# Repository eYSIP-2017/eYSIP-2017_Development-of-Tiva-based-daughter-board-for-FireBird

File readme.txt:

This folder contains the work done on Tiva based daughter board.
It includes manuals, experiment codes, schematics, report etc.

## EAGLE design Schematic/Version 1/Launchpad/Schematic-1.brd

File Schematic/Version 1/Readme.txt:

The following are the bugs in the version 1 of Plug and Play board and uC based board.

Bugs:

Plug and Play Board:
1. 7805 Placement: The 7805 was not positioned at the end. Becuase of
this there was no sucient space to add the heat sink.
2. Port Expander Naming: The names of port expander are interchanged
in the Daughter board. The names of port expander printed on the
Daughter board are interchanged. Port B is named as port A and vice
versa.
3. Switch Connection : The switch is used to connect the Ground of
Launchpad and Daughter board for programming. The connections of
this switch is incorrect.
4. The bot has to powered rst and then micro USB should be connected
to program the bot. This is because of the absence of switch explained
in the previous step
5. LCD starts displaying data on alternate press of reset button. It gets
initialised everytime but fails to display data.
6. Buzzer and red LED of TIVA launchad are on the same pin. Certain
motors pins and red and green LED pins also overlap.

uC based Board:
1. RX and TX LEDs: LEDs attached to RX and TX pins of serial com-
munication are not woring. The bot is able to communicate with the
laptop serial but the LEDs are not glowing.
2. Crystal Placement: The Crystal is placed far from the microcontroller.
Because of this the inductance of wires may eect the crysal frequency.
3. Heat Sink: The heat sink provided for LM1117 is not sucient.
4. Naming : The names of port expamders, servo headers, programming
headers are not printer on the board. The names of SCL and SDA pins
on the board is interchanged i.e SCL pin is printed as SDA and vice
versa.
5. The bot does not get programmed everytime because of connection
problems.(Resolderig the pins of uC might help solve the problem)
6. LCD starts displaying data on alternate press of reset button. It gets
initialised everytime but fails to display data.

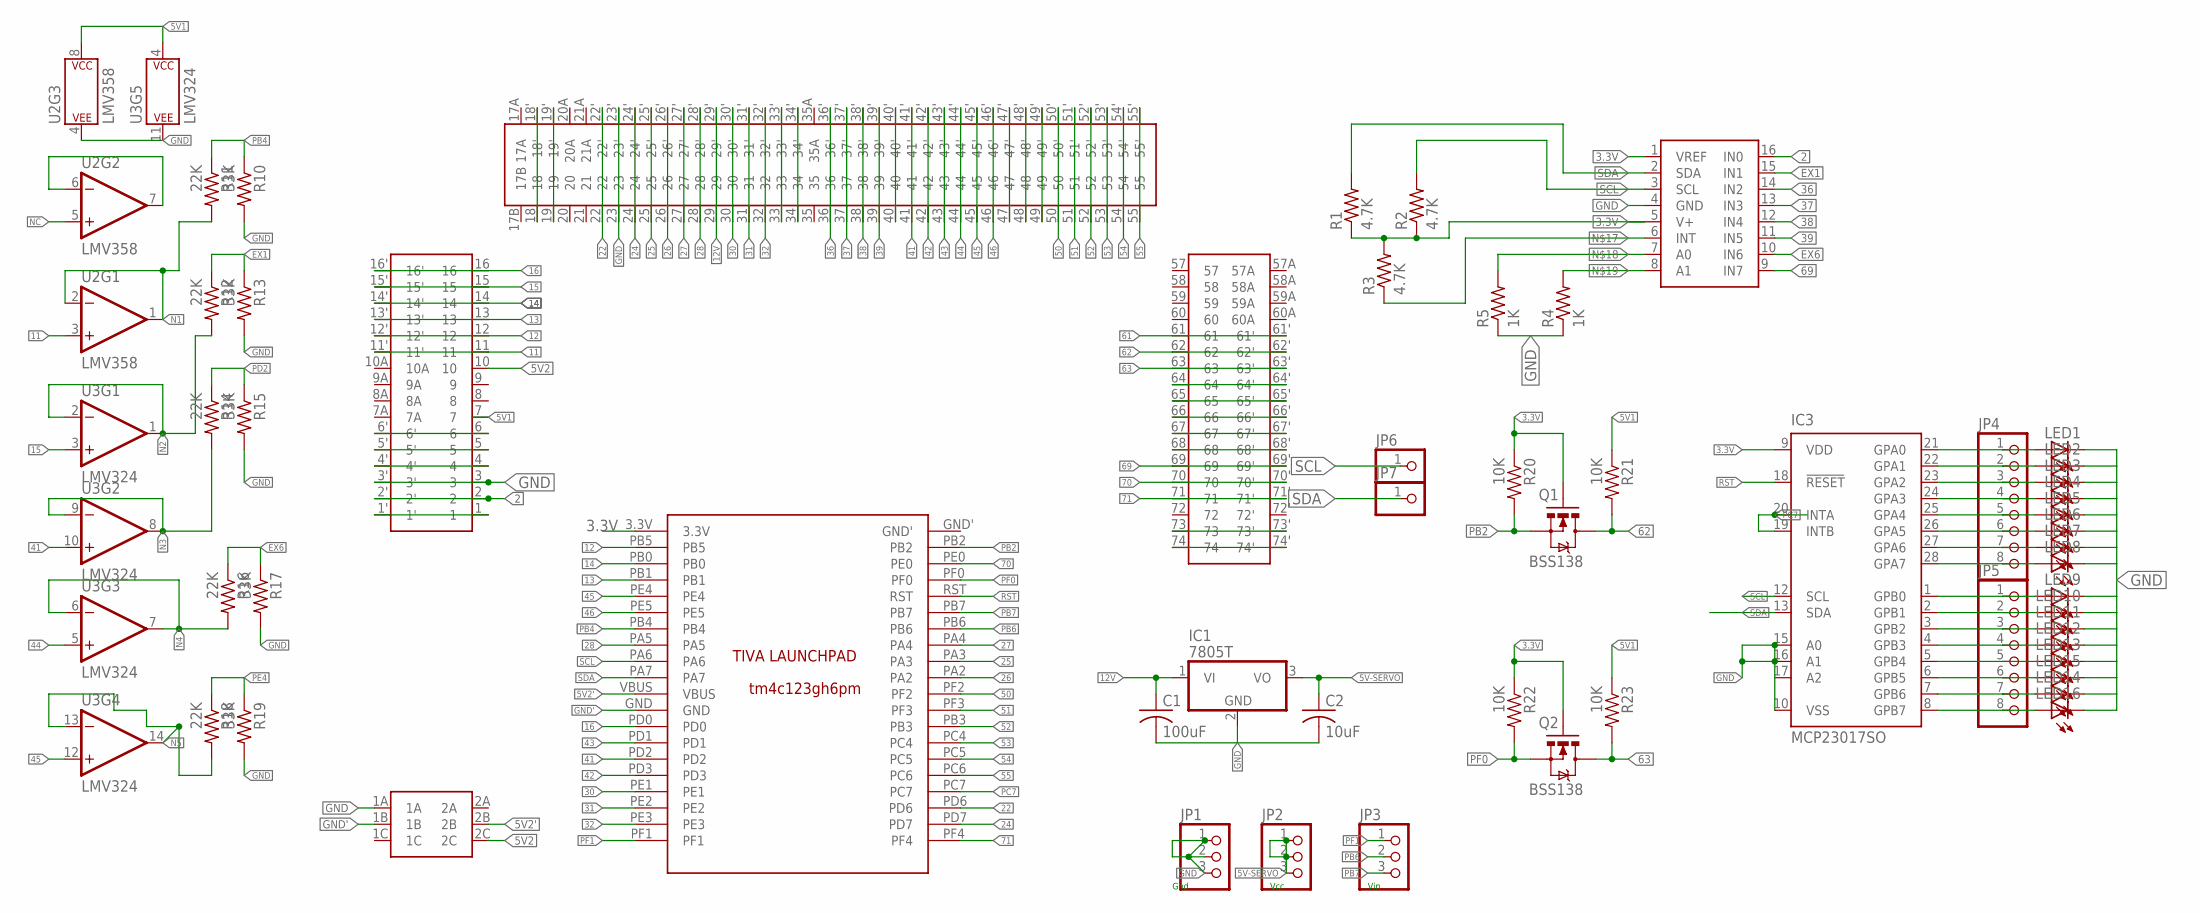
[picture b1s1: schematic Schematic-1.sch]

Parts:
C1: 100uF; C025-030X050
C2: 10uF; C025-030X050
IC1: 7805T; TO220H
IC3: MCP23017SO; SO28W
JP1, JP2, JP3: PINHD-1X3; 1X03
JP4, JP5: PINHD-1X8BIG; 1X08-BIG
JP6, JP7: PINHD-1X1; 1X01
LED1, LED2, LED3, LED4, LED5, LED6, LED7, LED8, LED9, LED10, LED11, LED12, LED13, LED14, LED15, LED16: LEDSMT1206; 1206
Q1, Q2: BSS138; SOT23-3
R1, R2, R3: 4.7K; M1206
R4, R5: 1K; M1206
R10, R13, R15, R17, R19: 33K; M1206
R11, R12, R14, R16, R18: 22K; M1206
R20, R21, R22, R23: 10K; 1206
U2: LMV358; SO08
U3: LMV324; SO14
U$1: DAUGHTERBOARDDAUGHTERBOARD; DAUGHTERBOARD
U$2: TIVA_LAUNCHPADTIVA_LAUNCHPAD; TIVA_LAUNCHPAD
U$3: SELF-LOCKING_SWITCHSELF-LOCKING_SWITCH; SELF-LOCKING_SWITCH
U$4: ADC128D818; ADC12_SD

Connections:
2: U$1.2, U$1.2', U$4.16 (IN0)
3.3V: IC3.9 (VDD), Q1.1 (G), Q2.1 (G), R1.1, R2.1, R3.2, R20.1, R22.1, U$2.3.3V, U$4.1 (VREF), U$4.5 (V+)
5V1: R21.1, R23.1, U2.8 (P$V+), U3.4 (P$V+), U$1.7
5V2: U$1.10, U$3.2C
5V2': U$2.VBUS, U$3.2B
5V-SERVO: C2.1, IC1.3 (VO), JP2.1, JP2.2, JP2.3
11: U2.3 (+IN), U$1.11, U$1.11'
12: U$1.12, U$1.12', U$2.PB5
12V: C1.1, IC1.1 (VI), U$1.29, U$1.29'
13: U$1.13, U$1.13', U$2.PB1
14: U$1.14, U$1.14', U$2.PB0
15: U3.3 (+IN), U$1.15, U$1.15'
16: U$1.16, U$1.16', U$2.PD0
22: U$1.22, U$1.22', U$2.PD6
24: U$1.24, U$1.24', U$2.PD7
25: U$1.25, U$1.25', U$2.PA3
26: U$1.26, U$1.26', U$2.PA2
27: U$1.27, U$1.27', U$2.PA4
28: U$1.28, U$1.28', U$2.PA5
30: U$1.30, U$1.30', U$2.PE1
31: U$1.31, U$1.31', U$2.PE2
32: U$1.32, U$1.32', U$2.PE3
36: U$1.36, U$1.36', U$4.14 (IN2)
37: U$1.37, U$1.37', U$4.13 (IN3)
38: U$1.38, U$1.38', U$4.12 (IN4)
39: U$1.39, U$1.39', U$4.11 (IN5)
41: U3.10 (+IN), U$1.41, U$1.41', U$2.PD2
42: U$1.42, U$1.42', U$2.PD3
43: U$1.43, U$1.43', U$2.PD1
44: U3.5 (+IN), U$1.44, U$1.44'
45: U3.12 (+IN), U$1.45, U$1.45', U$2.PE4
46: U$1.46, U$1.46', U$2.PE5
50: U$1.50, U$1.50', U$2.PF2
51: U$1.51, U$1.51', U$2.PF3
52: U$1.52, U$1.52', U$2.PB3
53: U$1.53, U$1.53', U$2.PC4
54: U$1.54, U$1.54', U$2.PC5
55: U$1.55, U$1.55', U$2.PC6
61: U$1.61, U$1.61'
62: Q1.3 (D), R21.2, U$1.62, U$1.62'
63: Q2.3 (D), R23.2, U$1.63, U$1.63'
69: U$1.69, U$1.69', U$4.9 (IN7)
70: U$1.70, U$1.70', U$2.PE0
71: U$1.71, U$1.71', U$2.PF4
EX1: R12.1, R13.1, U$4.15 (IN1)
EX6: R16.1, R17.1, U$4.10 (IN6)
GND: C1.2, C2.2, IC1.2 (GND), IC3.10 (VSS), IC3.15 (A0), IC3.16 (A1), IC3.17 (A2), JP1.1, JP1.2, JP1.3, LED1.C, LED2.C, LED3.C, LED4.C, LED5.C, LED6.C, LED7.C, LED8.C, LED9.C, LED10.C, LED11.C, LED12.C, LED13.C, LED14.C, LED15.C, LED16.C, R4.1, R5.1, R10.2, R13.2, R15.2, R17.2, R19.2, U2.4 (P$V-), U3.11 (P$V-), U$1.3, U$1.3', U$1.23, U$1.23', U$3.1A, U$4.4 (GND)
GND': U$2.GND, U$3.1B
N1: R11.2, U2.1 (OUT), U2.2 (-IN)
N2: R12.2, U3.1 (OUT), U3.2 (-IN)
N3: R14.2, U3.8 (OUT), U3.9 (-IN)
N4: R16.2, U3.6 (-IN), U3.7 (OUT)
N5: R18.2, U3.13 (-IN), U3.14 (OUT)
unnamed: U$1.1, U$1.1'
unnamed: U2.6 (-IN), U2.7 (OUT)
unnamed: IC3.21 (GPA0), JP4.1, LED1.A
unnamed: U$1.4, U$1.4'
unnamed: U$1.5, U$1.5'
unnamed: U$1.6, U$1.6'
unnamed: IC3.23 (GPA2), JP4.3, LED3.A
unnamed: IC3.24 (GPA3), JP4.4, LED4.A
unnamed: IC3.22 (GPA1), JP4.2, LED2.A
unnamed: IC3.25 (GPA4), JP4.5, LED5.A
unnamed: IC3.26 (GPA5), JP4.6, LED6.A
unnamed: IC3.27 (GPA6), JP4.7, LED7.A
unnamed: U$1.18, U$1.18'
unnamed: U$1.19, U$1.19'
unnamed: IC3.28 (GPA7), JP4.8, LED8.A
unnamed: R3.1, U$4.6 (INT)
unnamed: R5.2, U$4.7 (A0)
unnamed: R4.2, U$4.8 (A1)
unnamed: IC3.1 (GPB0), JP5.1, LED9.A
unnamed: IC3.2 (GPB1), JP5.2, LED10.A
unnamed: IC3.3 (GPB2), JP5.3, LED11.A
unnamed: IC3.4 (GPB3), JP5.4, LED12.A
unnamed: IC3.5 (GPB4), JP5.5, LED13.A
unnamed: IC3.6 (GPB5), JP5.6, LED15.A
unnamed: U$1.33, U$1.33'
unnamed: U$1.34, U$1.34'
unnamed: IC3.7 (GPB6), JP5.7, LED14.A
unnamed: IC3.8 (GPB7), JP5.8, LED16.A
unnamed: U$1.40, U$1.40'
unnamed: U$1.47, U$1.47'
unnamed: U$1.48, U$1.48'
unnamed: U$1.49, U$1.49'
unnamed: U$1.64, U$1.64'
unnamed: U$1.65, U$1.65'
unnamed: U$1.66, U$1.66'
unnamed: U$1.67, U$1.67'
unnamed: U$1.68, U$1.68'
unnamed: U$1.73, U$1.73'
unnamed: U$1.74, U$1.74'
NC: U2.5 (+IN)
PB2: Q1.2 (S), R20.2, U$2.PB2
PB4: R10.1, R11.1, U$2.PB4
PB6: JP3.2, U$2.PB6
PB7: JP3.3, U$2.PB7
PC7: IC3.19 (INTB), IC3.20 (INTA), U$2.PC7
PD2: R14.1, R15.1
PE4: R18.1, R19.1
PF0: Q2.2 (S), R22.2, U$2.PF0
PF1: JP3.1, U$2.PF1
RST: IC3.18 (!RESET), U$2.RST
SCL: IC3.12 (SCL), JP6.1, R2.2, U$2.PA6, U$4.3 (SCL)
SDA: IC3.13 (SDA), JP7.1, R1.2, U$2.PA7, U$4.2 (SDA)

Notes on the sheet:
Gnd
Vcc
Vin

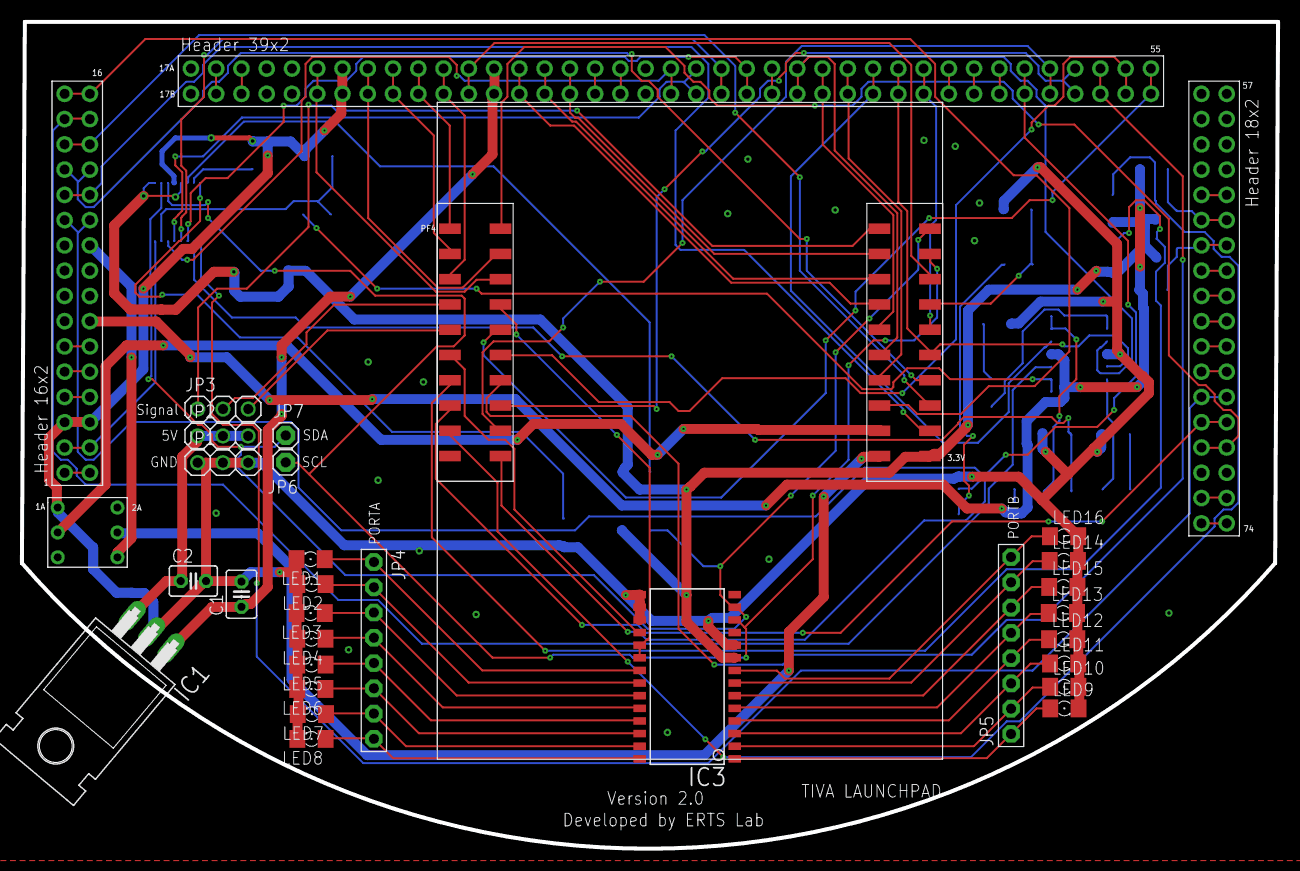
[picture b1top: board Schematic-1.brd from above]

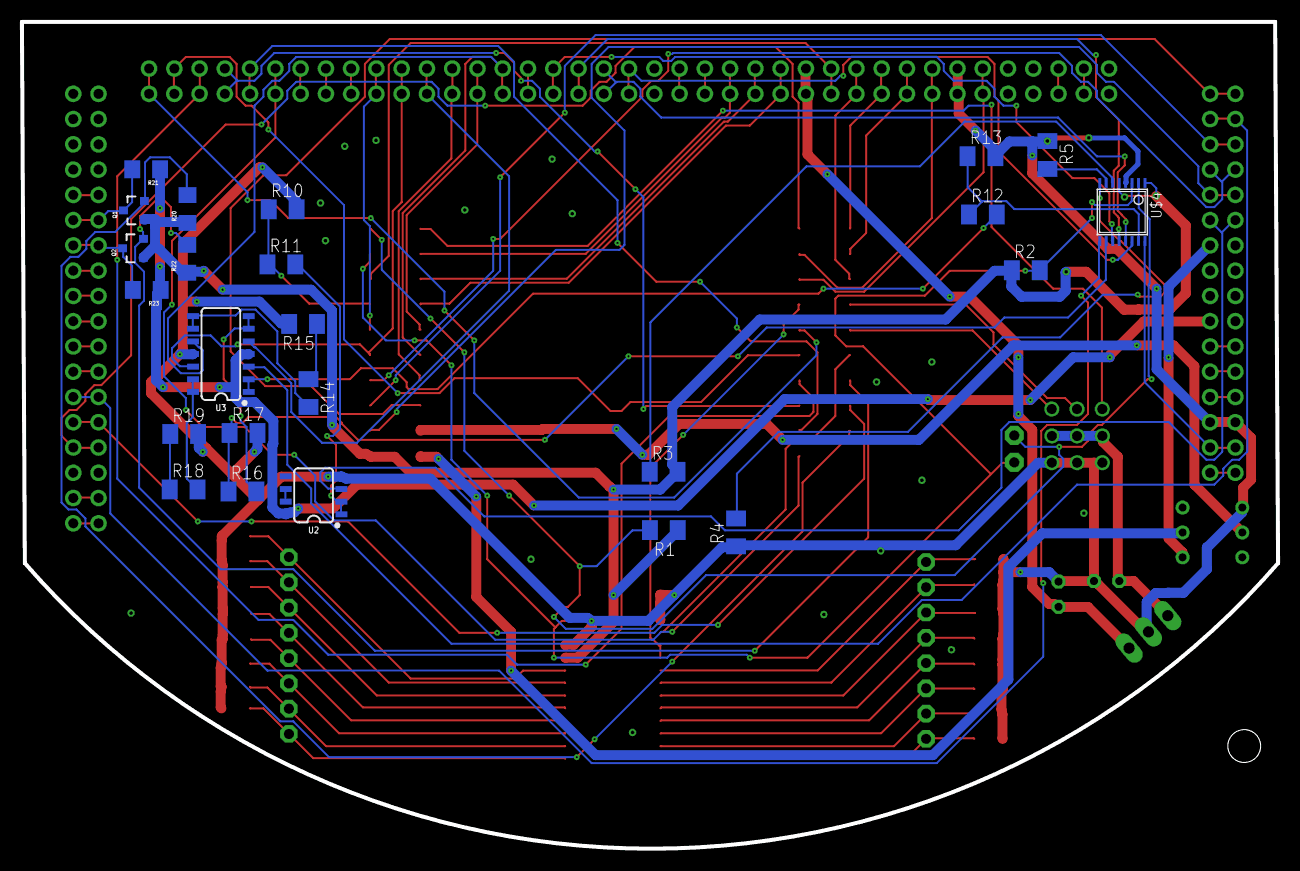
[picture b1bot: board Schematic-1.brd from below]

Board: 2 copper layers, 126.3 x 83.1 mm, 54 parts (24 on the bottom side), 104 nets.

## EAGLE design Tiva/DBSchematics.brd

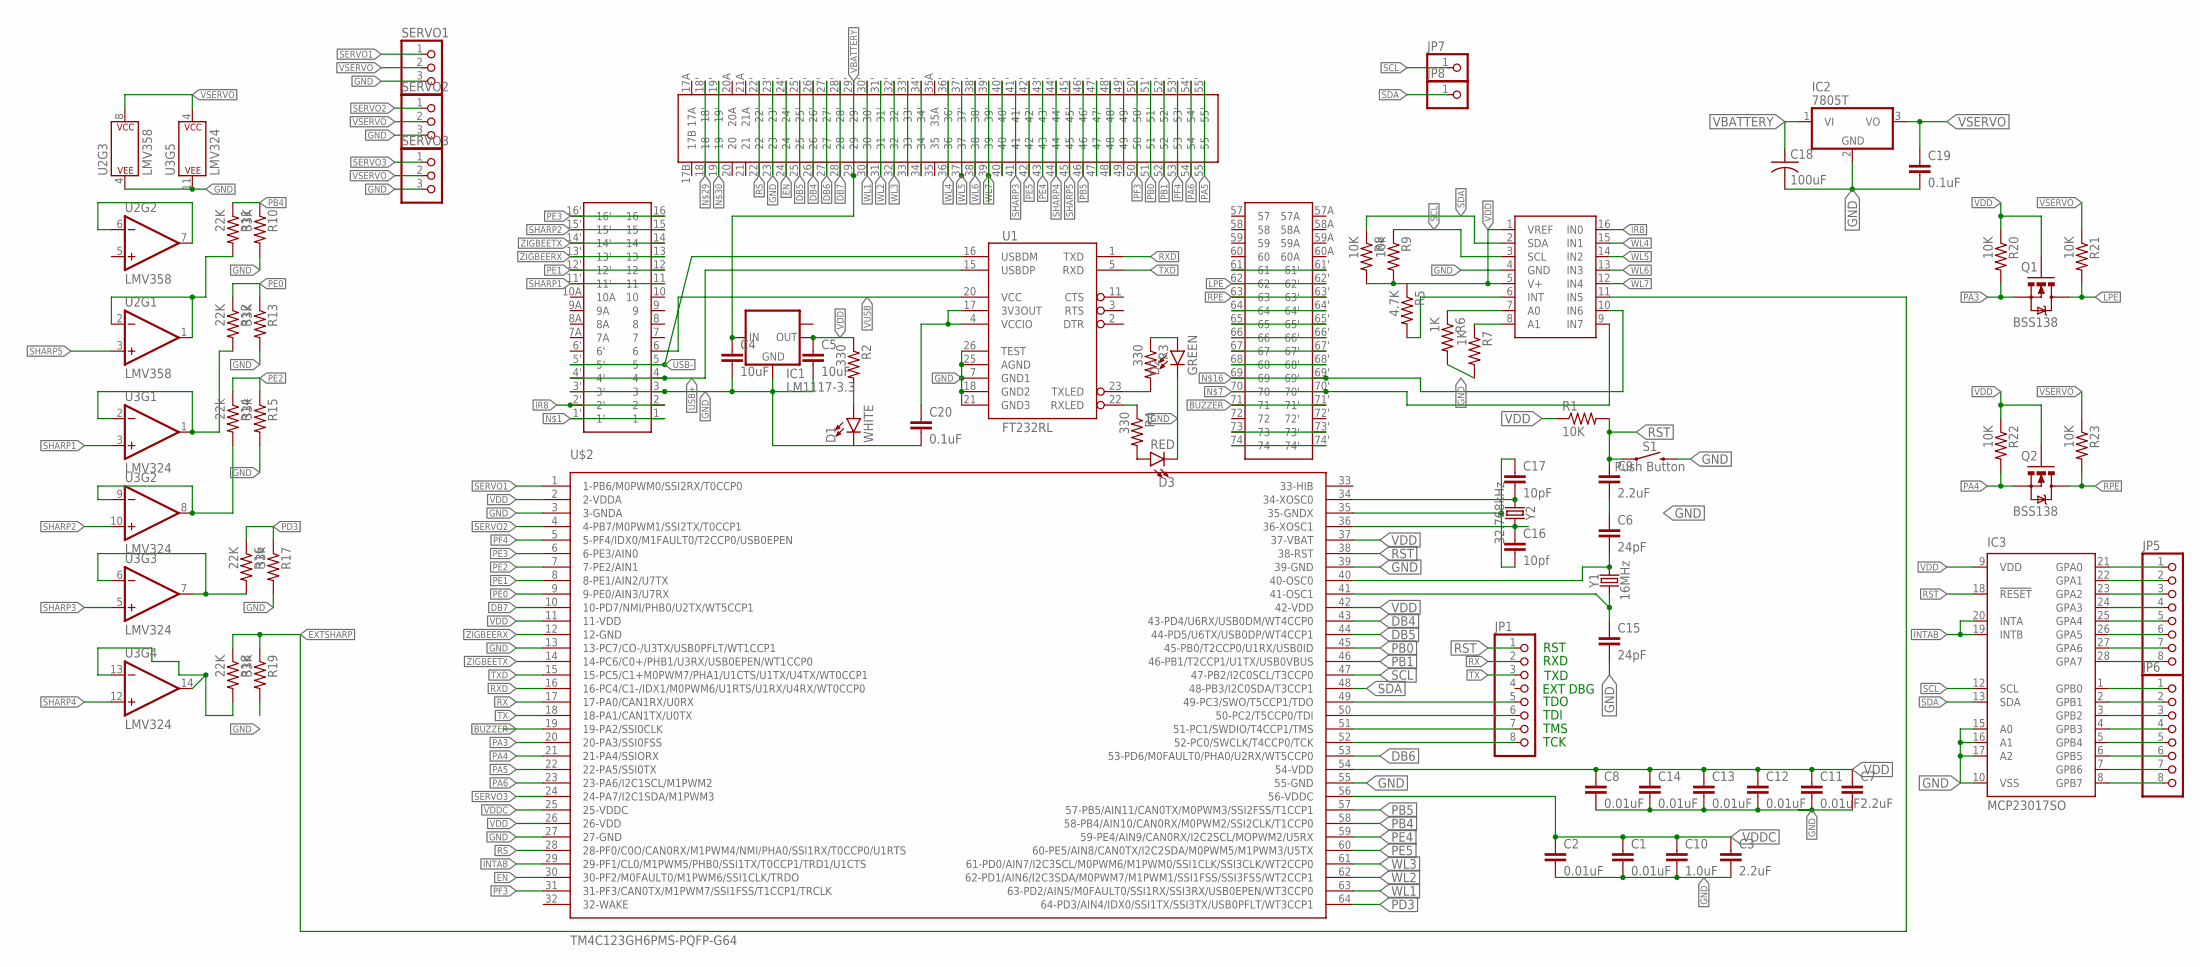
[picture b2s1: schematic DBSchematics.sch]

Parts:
C1, C2, C8, C11, C12, C13, C14: 0.01uF; 1206
C3, C7, C9: 2.2uF; 1206
C4, C5: 10uF; 1206
C6, C15: 24pF; 1206
C10: 1.0uF; 1206
C16: 10pf; 1206
C17: 10pF; 1206
C18: 100uF; C025-024X044
C19, C20: 0.1uF; 1206
D1: WHITE; LED-1206
D2: GREEN; LED-1206
D3: RED; LED-1206
IC1: LM1117-3.3; SOT223
IC2: 7805T; TO220H
IC3: MCP23017SO; SO28W
JP1: PINHD-1X8-3.5MM; 1X08-3.5MM
JP5, JP6: PINHD-1X8BIG; 1X08-BIG
JP7, JP8: PINHD-1X1; 1X01
Q1, Q2: BSS138; SOT23-3
R1, R8: 10K; M1206
R2, R3, R4: 330; M1206
R5: 4.7K; M1206
R6, R7: 1K; M1206
R9: 10k; M1206
R10, R13, R19: 33K; M1206
R11, R12, R16, R18: 22K; M1206
R14: 22k; M1206
R15, R17: 33k; M1206
R20, R21, R22, R23: 10K; 1206
S1: Push Button; TACTILE_SWITCH_PTH_6.0MM
SERVO1, SERVO2, SERVO3: PINHD-1X3; 1X03
U1: FT232RL; SSOP28DB
U2: LMV358; SO08
U3: LMV324; SO14
U$1: DAUGHTERBOARDDAUGHTERBOARD; DAUGHTERBOARD
U$2: TM4C123GH6PMS-PQFP-G64; LQFP
U$3: ADC128D818; ADC12_SD
Y1: 16MHz; HC49US
Y2: 32.768kHz; CRYSTAL-PTH-2X6-CYL

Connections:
BUZZER: U$1.71, U$1.71', U$2.19 (19-PA2/SSI0CLK)
DB4: U$1.26, U$1.26', U$2.43 (43-PD4/U6RX/USB0DM/WT4CCP0)
DB5: U$1.25, U$1.25', U$2.44 (44-PD5/U6TX/USB0DP/WT4CCP1)
DB6: U$1.27, U$1.27', U$2.53 (53-PD6/M0FAULT0/PHA0/U2RX/WT5CCP0)
DB7: U$1.28, U$1.28', U$2.10 (10-PD7/NMI/PHB0/U2TX/WT5CCP1)
EN: U$1.24, U$1.24', U$2.30 (30-PF2/M0FAULT0/M1PWM6/SSI1CLK/TRDO)
EXTSHARP: R18.1, R19.1, U$3.11 (IN5)
FDSFSDF: R12.2, U3.1 (OUT), U3.2 (-IN)
GND: C1.2, C2.2, C3.2, C4.2, C5.2, C6.1, C7.2, C8.2, C9.2, C10.2, C11.2, C12.2, C13.2, C14.2, C15.2, C18.2, C19.2, C20.2, D1.C, D2.C, D3.C, IC1.1 (GND), IC2.2 (GND), IC3.10 (VSS), IC3.15 (A0), IC3.16 (A1), IC3.17 (A2), JP1.4, R6.2, R7.2, R10.2, R13.2, R15.2, R17.2, R19.2, S1.3 (2), SERVO1.3, SERVO2.3, SERVO3.3, U1.7 (GND1), U1.18 (GND2), U1.21 (GND3), U1.25 (AGND), U1.26 (TEST), U2.4 (P$V-), U3.11 (P$V-), U$1.3, U$1.3', U$1.23, U$1.23', U$2.3 (3-GNDA), U$2.12 (12-GND), U$2.27 (27-GND), U$2.39 (39-GND), U$2.55 (55-GND), U$3.4 (GND); also elsewhere on the board
GNDX: C16.2, C17.1, U$2.35 (35-GNDX)
HGHJ: R11.2, U2.1 (OUT), U2.2 (-IN)
INTAB: IC3.19 (INTB), IC3.20 (INTA), U$2.29 (29-PF1/CL0/M1PWM5/PHB0/SSI1TX/T0CCP1/TR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)
IR8: U$1.2, U$1.2', U$3.16 (IN0)
LPE: Q1.3 (D), R21.2, U$1.62, U$1.62'
unnamed: U$1.1, U$1.1'
unnamed: IC3.21 (GPA0), JP5.1
unnamed: C6.2, U$2.40 (40-OSC0), Y1.2
unnamed: IC3.22 (GPA1), JP5.2
unnamed: U2.6 (-IN), U2.7 (OUT)
unnamed: U$1.70, U$1.70', U$3.9 (IN7)
unnamed: IC3.23 (GPA2), JP5.3
unnamed: IC3.24 (GPA3), JP5.4
unnamed: IC3.25 (GPA4), JP5.5
unnamed: JP1.8, U$2.52 (52-PC0/SWCLK/T4CCP0/TCK)
unnamed: U$1.74, U$1.74'
unnamed: U$1.73, U$1.73'
unnamed: R18.2, U3.13 (-IN), U3.14 (OUT)
unnamed: JP1.7, U$2.51 (51-PC1/SWDIO/T4CCP1/TMS)
unnamed: U$1.69, U$1.69', U$3.10 (IN6)
unnamed: U$1.68, U$1.68'
unnamed: U$1.67, U$1.67'
unnamed: U$1.66, U$1.66'
unnamed: U$1.65, U$1.65'
unnamed: U$1.64, U$1.64'
unnamed: R6.1, U$3.7 (A0)
unnamed: IC3.26 (GPA5), JP5.6
unnamed: U$1.61, U$1.61'
unnamed: JP1.6, U$2.50 (50-PC2/T5CCP0/TDI)
unnamed: D1.A, R2.2
unnamed: C17.2, U$2.34 (34-XOSC0), Y2.1
unnamed: C16.1, U$2.36 (36-XOSC1), Y2.2
unnamed: U$1.18, U$1.18'
unnamed: U$1.19, U$1.19'
unnamed: JP1.5, U$2.49 (49-PC3/SWO/T5CCP1/TDO)
unnamed: IC3.27 (GPA6), JP5.7
unnamed: IC3.28 (GPA7), JP5.8
unnamed: IC3.1 (GPB0), JP6.1
unnamed: IC3.2 (GPB1), JP6.2
unnamed: IC3.3 (GPB2), JP6.3
unnamed: IC3.4 (GPB3), JP6.4
unnamed: IC3.5 (GPB4), JP6.5
unnamed: IC3.6 (GPB5), JP6.6
unnamed: IC3.7 (GPB6), JP6.7
unnamed: IC3.8 (GPB7), JP6.8
unnamed: U$1.33, U$1.33'
unnamed: U$1.34, U$1.34'
unnamed: U$1.40, U$1.40'
unnamed: U$1.47, U$1.47'
unnamed: U$1.48, U$1.48'
unnamed: U$1.49, U$1.49'
unnamed: R4.1, U1.22 (RXLED)
unnamed: R3.2, U1.23 (TXLED)
unnamed: D3.A, R4.2
unnamed: D2.A, R3.1
unnamed: R5.2, U$3.6 (INT)
unnamed: R7.1, U$3.8 (A1)
unnamed: C20.1, U1.4 (VCCIO), U1.17 (3V3OUT)
NO: C15.1, U$2.41 (41-OSC1), Y1.1
PA3: Q1.2 (S), R20.2, U$2.20 (20-PA3/SSI0FSS)
PA4: Q2.2 (S), R22.2, U$2.21 (21-PA4/SSIORX)
PA5: U$1.55, U$1.55', U$2.22 (22-PA5/SSI0TX)
PA6: U$1.54, U$1.54', U$2.23 (23-PA6/I2C1SCL/M1PWM2)
PB0: U$1.51, U$1.51', U$2.45 (45-PB0/T2CCP0/U1RX/USB0ID)
PB1: U$1.52, U$1.52', U$2.46 (46-PB1/T2CCP1/U1TX/USB0VBUS)
PB4: R10.1, R11.1, U$2.58 (58-PB4/AIN10/CAN0RX/M0PWM2/SSI2CLK/T1CC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)
PB5: U$1.46, U$1.46', U$2.57 (57-PB5/AIN11/CAN0TX/M0PWM3/SSI2FSS/T1CC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)
PD3: R16.1, R17.1, U$2.64 (64-PD3/AIN4/IDX0/SSI1TX/SSI3TX/USB0PFLT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)
PE0: R12.1, R13.1, U$2.9 (9-PE0/AIN3/U7RX)
PE1: U$1.12, U$1.12', U$2.8 (8-PE1/AIN2/U7TX)
PE2: R14.1, R15.1, U$2.7 (7-PE2/AIN1)
PE3: U$1.16, U$1.16', U$2.6 (6-PE3/AIN0)
PE4: U$1.43, U$1.43', U$2.59 (59-PE4/AIN9/CAN0RX/I2C2SCL/MOPWM2/U5RX)
PE5: U$1.42, U$1.42', U$2.60 (60-PE5/AIN8/CAN0TX/I2C2SDA/M0PWM5/M1PWM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)
PF3: U$1.50, U$1.50', U$2.31 (31-PF3/CAN0TX/M1PWM7/SSI1FSS/T1CCP1/TRC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)
PF4: U$1.53, U$1.53', U$2.5 (5-PF4/IDX0/M1FAULT0/T2CCP0/USB0EPEN)
RPE: Q2.3 (D), R23.2, U$1.63, U$1.63'
RS: U$1.22, U$1.22', U$2.28 (28-PF0/C0O/CAN0RX/M1PWM4/NMI/PHA0/SSI1R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)
RST: C9.1, IC3.18 (!RESET), JP1.1, R1.2, S1.1, U$2.38 (38-RST)
RX: JP1.2, U$2.17 (17-PA0/CAN1RX/U0RX)
RXD: U1.1 (TXD), U$2.16 (16-PC4/C1-/IDX1/M0PWM6/U1RTS/U1RX/U4RX/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)
SCL: IC3.12 (SCL), JP7.1, R9.1, U$2.47 (47-PB2/I2C0SCL/T3CCP0), U$3.3 (SCL)
SDA: IC3.13 (SDA), JP8.1, R8.1, U$2.48 (48-PB3/I2C0SDA/T3CCP1), U$3.2 (SDA)
SDFSDFSD: R14.2, U3.8 (OUT), U3.9 (-IN)
SERVO1: SERVO1.1, U$2.1 (1-PB6/M0PWM0/SSI2RX/T0CCP0)
SERVO2: SERVO2.1, U$2.4 (4-PB7/M0PWM1/SSI2TX/T0CCP1)
SERVO3: SERVO3.1, U$2.24 (24-PA7/I2C1SDA/M1PWM3)
SHARP1: U3.3 (+IN), U$1.11, U$1.11'
SHARP2: U3.10 (+IN), U$1.15, U$1.15'
SHARP3: U3.5 (+IN), U$1.41, U$1.41'
SHARP4: U3.12 (+IN), U$1.44, U$1.44'
SHARP5: U2.3 (+IN), U$1.45, U$1.45'
TX: JP1.3, U$2.18 (18-PA1/CAN1TX/U0TX)
TXD: U1.5 (RXD), U$2.15 (15-PC5/C1+M0PWM7/PHA1/U1CTS/U1TX/U4TX/W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)
USB+: U1.15 (USBDP), U$1.4, U$1.4'
USB-: U1.16 (USBDM), U$1.5, U$1.5'
VBATTERY: C4.1, C18.1, IC1.3 (IN), IC2.1 (VI), U$1.29, U$1.29'
VDD: C5.1, C7.1, C8.1, C11.1, C12.1, C13.1, C14.1, IC1.2 (OUT), IC3.9 (VDD), Q1.1 (G), Q2.1 (G), R1.1, R2.1, R5.1, R8.2, R9.2, R20.1, R22.1, U$2.2 (2-VDDA), U$2.11 (11-VDD), U$2.26 (26-VDD), U$2.37 (37-VBAT), U$2.42 (42-VDD), U$2.54 (54-VDD), U$3.1 (VREF), U$3.5 (V+); also elsewhere on the board
VDDC: C1.1, C2.1, C3.1, C10.1, U$2.25 (25-VDDC), U$2.56 (56-VDDC)
VSERVO: C19.1, IC2.3 (VO), R21.1, R23.1, SERVO1.2, SERVO2.2, SERVO3.2, U2.8 (P$V+), U3.4 (P$V+); also elsewhere on the board
VUSB: U1.20 (VCC), U$1.6
WL1: U$1.30, U$1.30', U$2.63 (63-PD2/AIN5/M0FAULT0/SSI1RX/SSI3RX/USB0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)
WL2: U$1.31, U$1.31', U$2.62 (62-PD1/AIN6/I2C3SDA/M0PWM7/M1PWM1/SSI1F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)
WL3: U$1.32, U$1.32', U$2.61 (61-PD0/AIN7/I2C3SCL/M0PWM6/M1PWM0/SSI1C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)
WL4: U$1.36, U$1.36', U$3.15 (IN1)
WL5: U$1.37, U$1.37', U$3.14 (IN2)
WL6: U$1.38, U$1.38', U$3.13 (IN3)
WL7: U$1.39, U$1.39', U$3.12 (IN4)
XXVX: R16.2, U3.6 (-IN), U3.7 (OUT)
ZIGBEERX: U$1.13, U$1.13', U$2.13 (13-PC7/CO-/U3TX/USB0PFLT/WT1CCP1)
ZIGBEETX: U$1.14, U$1.14', U$2.14 (14-PC6/C0+/PHB1/U3RX/USB0EPEN/WT1CCP0)

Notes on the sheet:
TCK
TMS
TDI
TDO
RST
TXD
RXD
EXT DBG

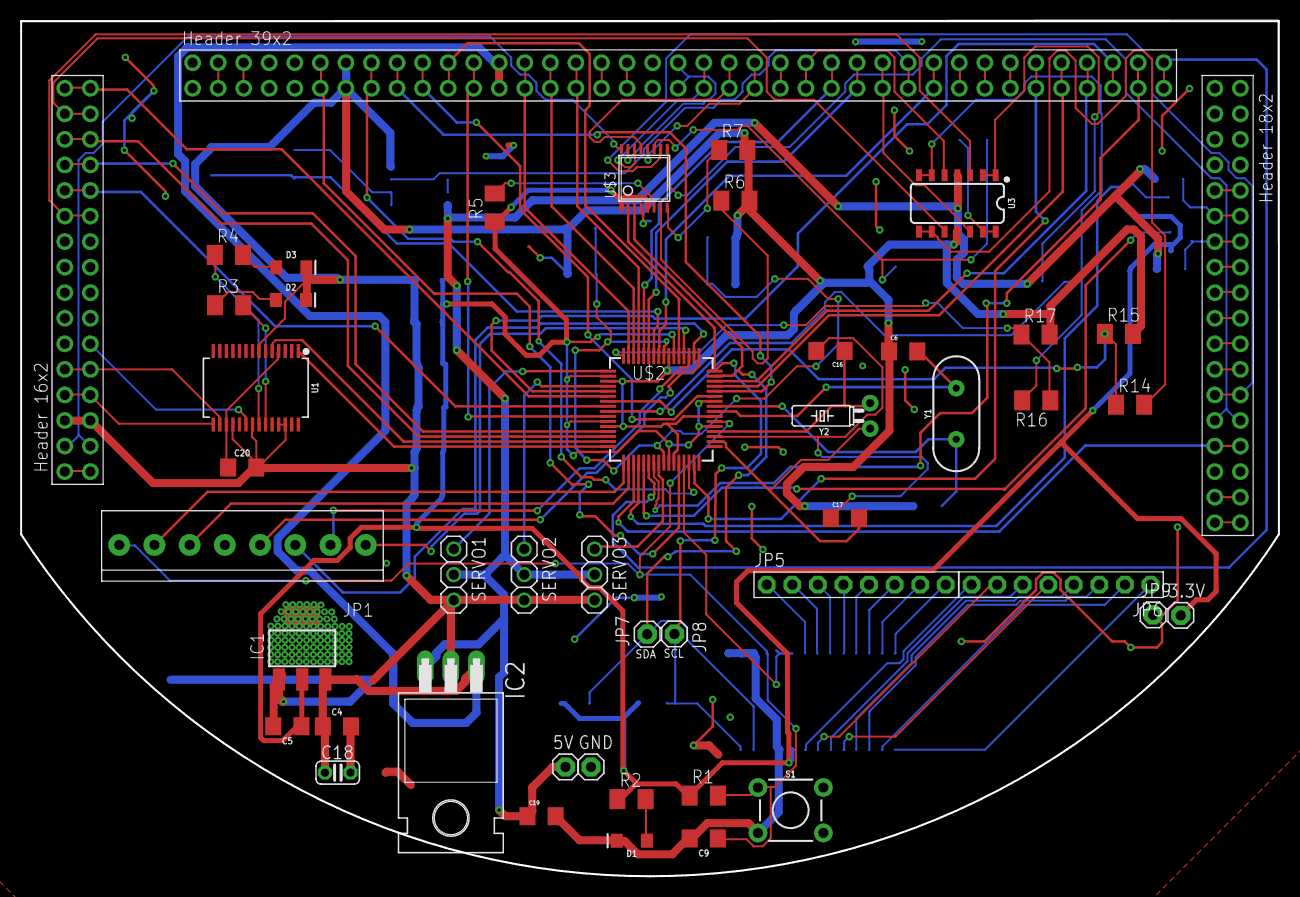
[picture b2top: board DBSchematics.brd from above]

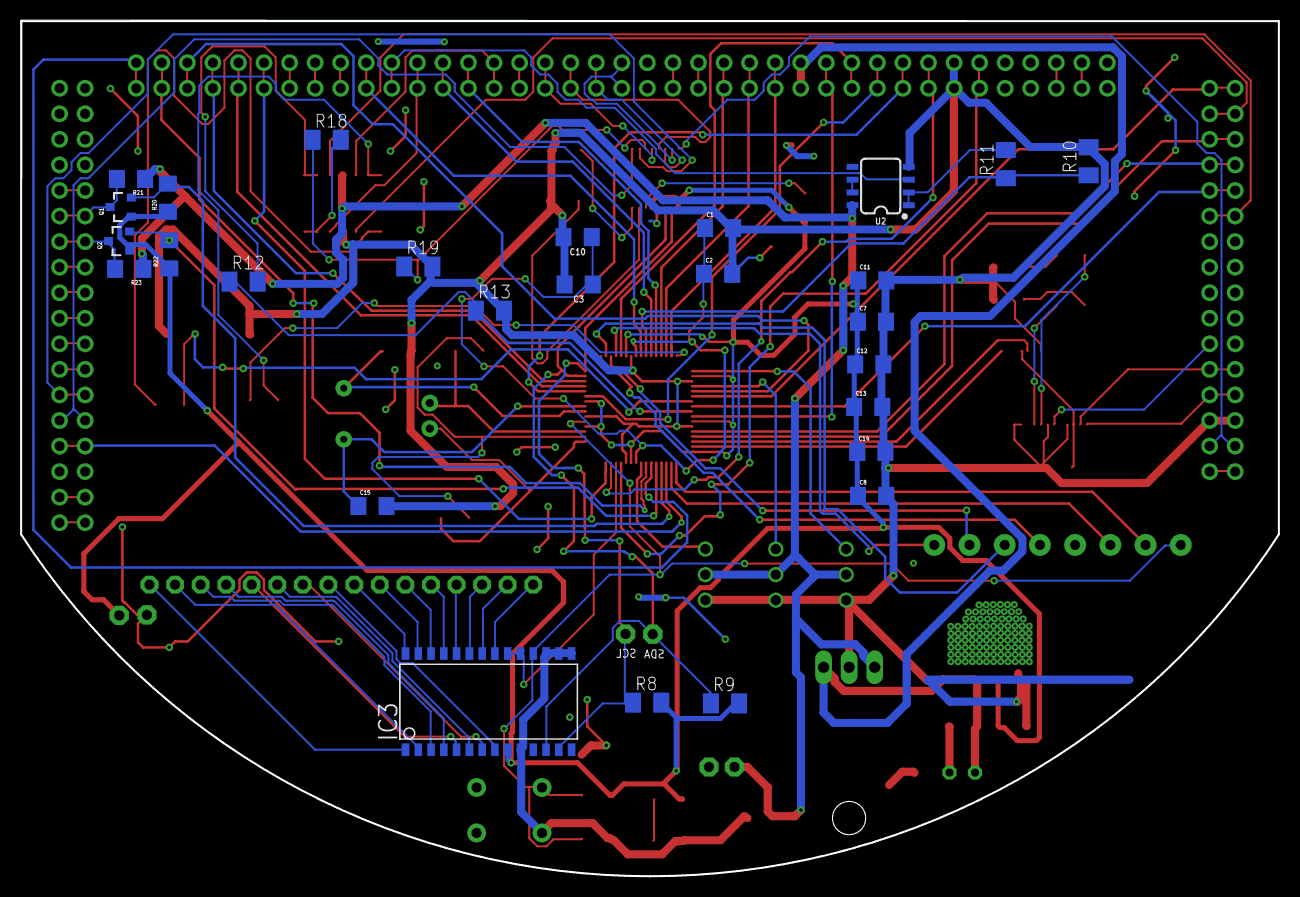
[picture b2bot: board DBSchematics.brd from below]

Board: 2 copper layers, 125.0 x 85.0 mm, 72 parts (27 on the bottom side), 120 nets.

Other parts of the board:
3.3V, 5V: 1X01
GND: 1X01
JP9: GND; 1X01

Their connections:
GND: GND.1, JP9.1; also elsewhere on the board
VDD: 3.3V.1; also elsewhere on the board
VSERVO: 5V.1; also elsewhere on the board

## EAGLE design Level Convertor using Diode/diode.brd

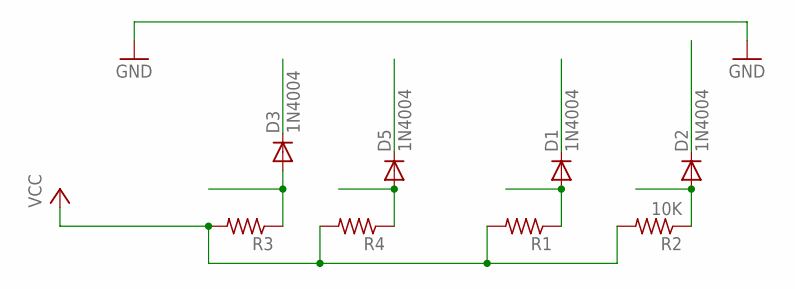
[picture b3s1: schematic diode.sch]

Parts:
D1, D2, D3, D5: 1N4004; DO41-10
R1, R3, R4: R-US_0204/5; 0204/5
R2: 10K; 0204/5

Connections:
IN1: D3.C
IN2: D5.C
IN3: D1.C
IN4: D2.C
OUT1: D3.A, R3.1
OUT2: D5.A, R4.1
OUT3: D1.A, R1.1
OUT4: D2.A, R2.1
VCC: R1.2, R2.2, R3.2, R4.2

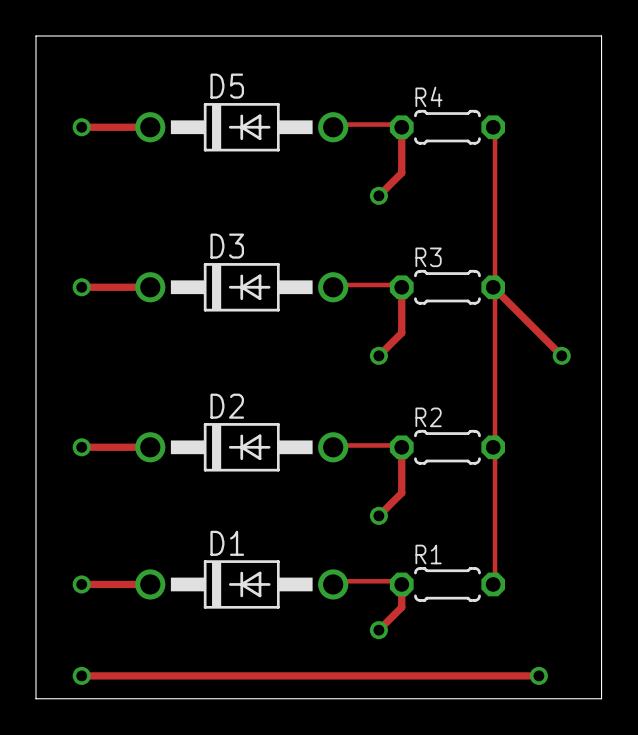
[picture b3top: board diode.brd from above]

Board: 2 copper layers, 31.4 x 36.8 mm, 8 parts (0 on the bottom side), 5 nets.

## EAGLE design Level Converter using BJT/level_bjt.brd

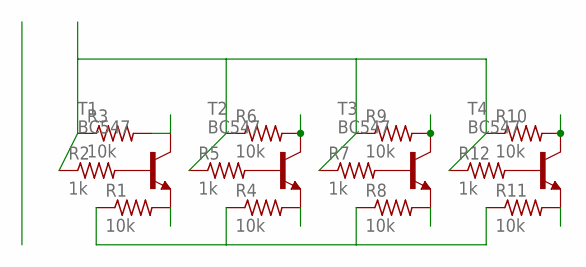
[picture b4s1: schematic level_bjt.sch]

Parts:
R1, R3, R4, R6, R8, R9, R10, R11: 10k; 0204/5
R2, R5, R7, R12: 1k; 0204/5
T1, T2, T3, T4: BC547; TO92

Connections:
unnamed: R2.2, T1.2 (B)
unnamed: R6.2, R9.2, R10.2, T2.3 (C), T3.3 (C), T4.3 (C)
unnamed: R5.2, T2.2 (B)
unnamed: R1.2, T1.1 (E)
unnamed: R7.2, T3.2 (B)
unnamed: R1.1, R4.1, R8.1, R11.1
unnamed: R4.2, T2.1 (E)
unnamed: R8.2, T3.1 (E)
unnamed: R2.1, R3.1, R5.1, R6.1, R7.1, R9.1, R10.1, R12.1
unnamed: R12.2, T4.2 (B)
unnamed: R11.2, T4.1 (E)
unnamed: R3.2, T1.3 (C)

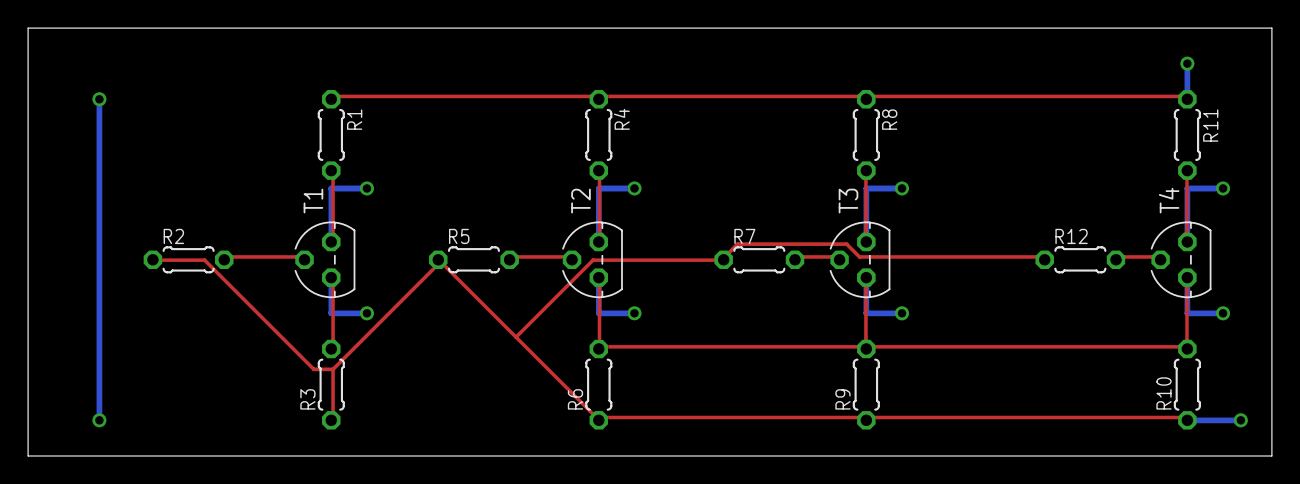
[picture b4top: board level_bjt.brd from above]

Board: 2 copper layers, 88.6 x 30.5 mm, 16 parts (0 on the bottom side), 12 nets.

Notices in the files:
parts and their libraries:
SparkFun-IC-Amplifiers: Licensing: Creative Commons ShareAlike 4.0 International - https://creativecommons.org/licenses/by-sa/4.0
